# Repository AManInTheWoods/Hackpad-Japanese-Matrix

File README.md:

# CreatePad V1
CreatePad (formerly named "Hackpad V2.1 Japanese Matrix" and "Macropad Proto V1") is a multipurpose productivity macro pad with a 3x3 switch layout, two rotary encoders, an OLED screen and uses QMK firmware. Under the hood is a Japanese Duplex Matrix that made the large amount of inputs (15 in total, including both of the encoders' buttons!) possible. More info on that below.

<H2>
Features: 
</H2>

  * 11 total switches (3x3 MX + 2 knobs)
  
  * A 0.91 inch OLED display
    
  * 10 customizable profiles with VIA support
  
  * Slanted case design for better (my personal) comfort :)

<H2>
CAD Model, Made in Fusion360 (the free version):
</H2>

<H3>This is the overall CAD design of CreatePad:</H3> 

<H3>This is the separated (top case, PCB, bottom case) bodies:</H3> 

<H2>Schematic & PCB (Made in KiCAD):</H2>

<H3>Schematic:</H3>

<H4>"Behold, The Japanese Duplex Matrix"</H4>

<H3>PCB:</H3>

*<H4> I had such a dilemma making sure everything is aligned and symmetrical (some still probably aren't) </H4>*

<H2>Firmware Overview:</H2>

CreatePad uses custom QMK firmware (because the matrix used is different from a traditional matrix) and is highly customizable, even the OLED can be configured using it! The attatched firmware (as of now) can store up to 10 unique, fully customizable configurations (even the knobs' functions!) through VIA.

<H2>The Japanese Duplex Matrix</H2>

Since the XIAO RP2040 only has 14 pins and only 5 of them are left for button inputs, I had to pick between two choices: 1. Reduce the amount of total physical inputs or 2. Find out if there's another type of matrix that reduces the amount of pins even further than that of a traditional matrix. Turns out there is such a thing! It's called a Japanese Duplex Matrix. Everything about it can be read on this webpage: https://kbd.news/The-Japanese-duplex-matrix-1391.html#jpduplex .

In a nutshell, according to the webpage, unlike a traditional keyboard matrix, the custom QMK firmware scans the matrix in both directions! First COL2ROW, then ROW2COL, in succession. "The trick lies in the direction of diodes: two columns are connected to the same COL pin, but one column has diodes pointing in one direction, while switches in the second column have diodes pointing to the opposite direction. This way the matrix can be scanned in both ways, checking half of the switches on the COL2ROW and another half on the ROW2COL iteration." Compared to a traditional matrix, the amount of pins needed have been significant reduced, making it exactly needing only 5 pins! No extra rows or columns needed.

<H2>BOM:</H2>

* 1x Seeed XIAO RP2040 MCU

* 9x MX-Style Switches

* 2x EC11 Rotary Encoders

* 2x Rotary Encoder Knobs

* 11x Through-hole 1N4148 Diodes

* 1x 0.91 Inch OLED Display

* 9x white DSA keycaps

* 4x M3x16mm screws

that's about it for now :). I've learned so much during the process of designing this project, I can't wait to assemble it in the future!

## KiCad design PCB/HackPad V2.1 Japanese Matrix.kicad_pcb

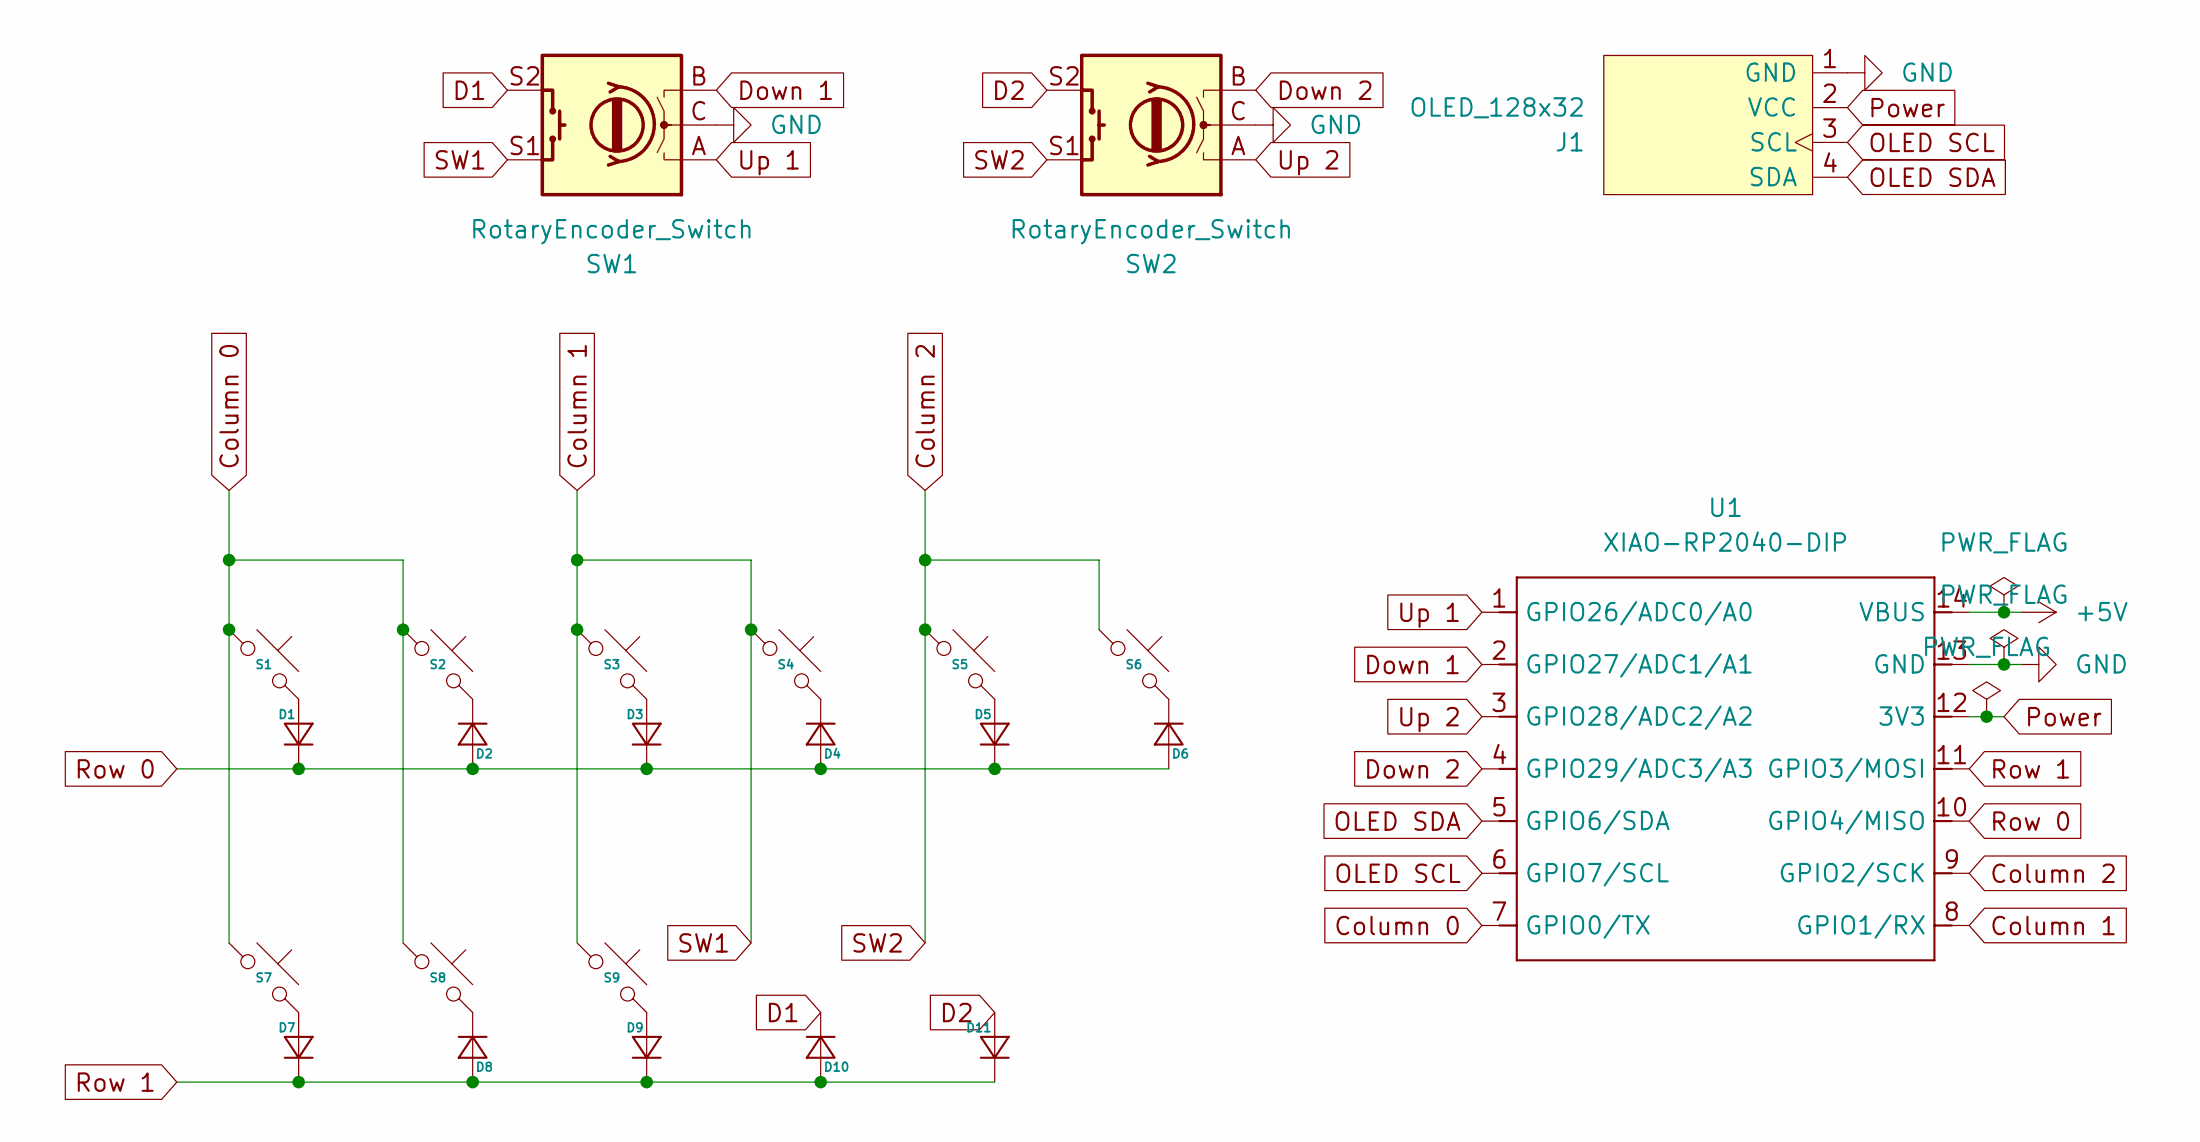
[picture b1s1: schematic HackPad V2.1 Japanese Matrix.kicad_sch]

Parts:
D1, D2, D3, D4, D5, D6, D7, D8, D9, D10, D11: Diode_DO-35
J1: OLED_128x32
S1, S2, S3, S4, S5, S6, S7, S8, S9: MX_PCB_1.00u
SW1, SW2: RotaryEncoder_Switch; RotaryEncoder_Alps_EC11E-Switch_Vertical_H20mm
U1: XIAO-RP2040-DIP

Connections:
+5V: U1.14 (VBUS)
Column 0: S1.1, S2.1, S7.1, S8.1, U1.7 (GPIO0/TX)
Column 1: S3.1, S4.1, S9.1, SW1.S1, U1.8 (GPIO1/RX)
Column 2: S5.1, S6.1, SW2.S1, U1.9 (GPIO2/SCK)
D1: D10.1 (K), SW1.S2
D2: D11.2 (A), SW2.S2
Down 1: SW1.B, U1.2 (GPIO27/ADC1/A1)
Down 2: SW2.B, U1.4 (GPIO29/ADC3/A3)
GND: J1.1 (GND), SW1.C, SW2.C, U1.13 (GND)
unnamed: D1.2 (A), S1.2
unnamed: D2.1 (K), S2.2
unnamed: D3.2 (A), S3.2
unnamed: D4.1 (K), S4.2
unnamed: D5.2 (A), S5.2
unnamed: D6.1 (K), S6.2
unnamed: D7.2 (A), S7.2
unnamed: D8.1 (K), S8.2
unnamed: D9.2 (A), S9.2
OLED SCL: J1.3 (SCL), U1.6 (GPIO7/SCL)
OLED SDA: J1.4 (SDA), U1.5 (GPIO6/SDA)
Power: J1.2 (VCC), U1.12 (3V3)
Row 0: D1.1 (K), D2.2 (A), D3.1 (K), D4.2 (A), D5.1 (K), D6.2 (A), U1.10 (GPIO4/MISO)
Row 1: D7.1 (K), D8.2 (A), D9.1 (K), D10.2 (A), D11.1 (K), U1.11 (GPIO3/MOSI)
Up 1: SW1.A, U1.1 (GPIO26/ADC0/A0)
Up 2: SW2.A, U1.3 (GPIO28/ADC2/A2)

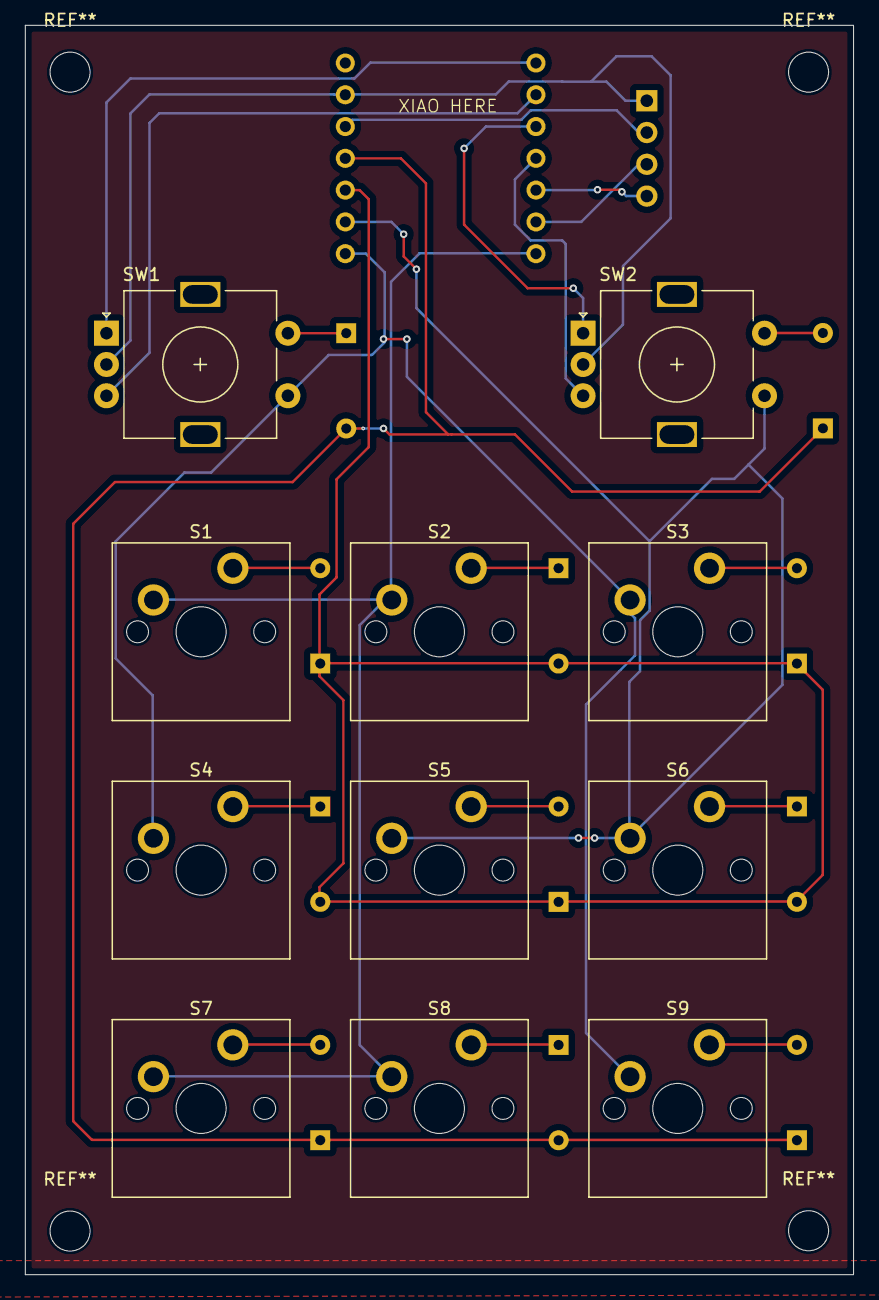
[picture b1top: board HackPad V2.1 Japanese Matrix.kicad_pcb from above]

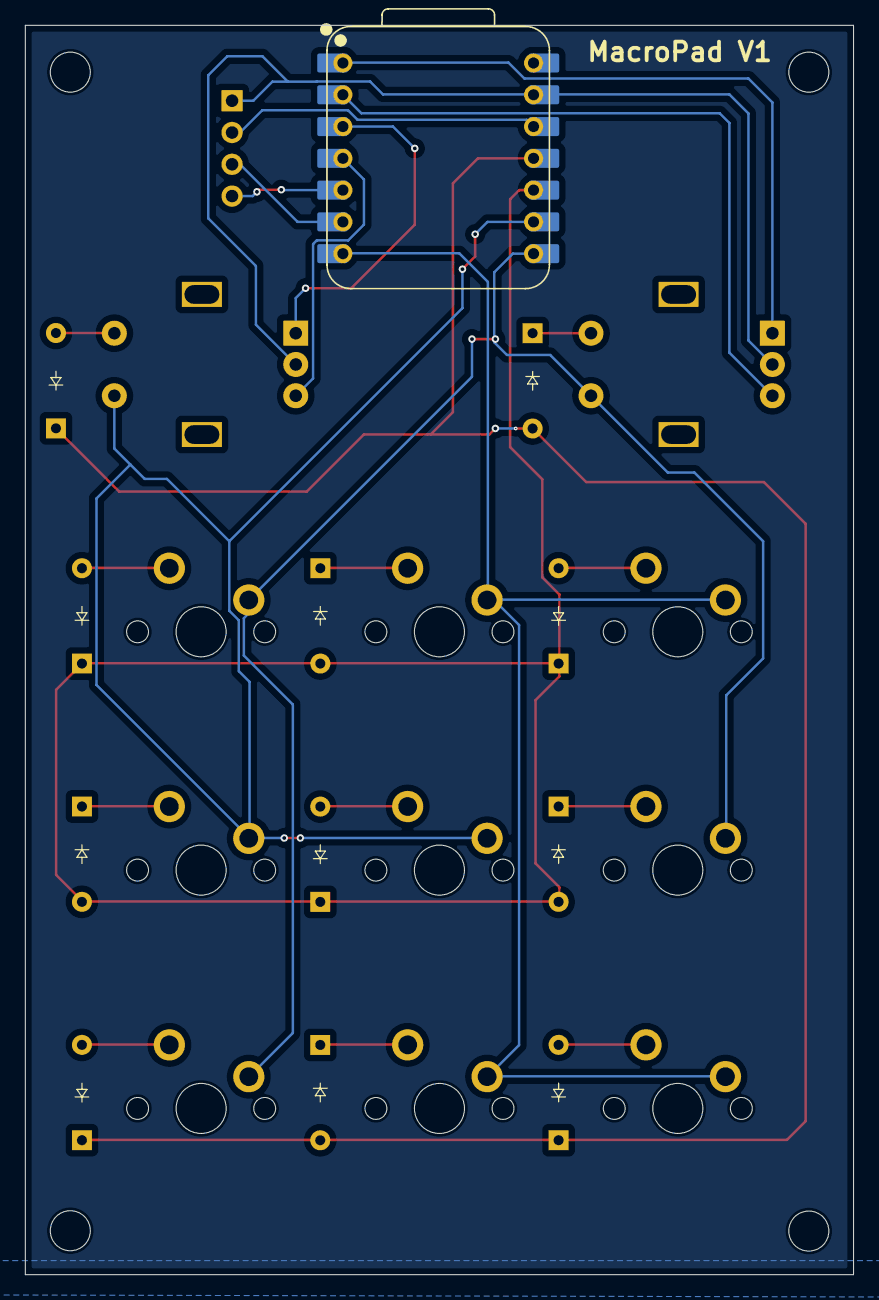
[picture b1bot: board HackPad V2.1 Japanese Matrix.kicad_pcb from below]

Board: 2 copper layers, 66.2 x 99.9 mm, 24 parts (12 on the bottom side), 24 nets.

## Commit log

2026-03-03 Create CAD
2026-03-03 Create ...
2026-03-04 Create fdsfs
2026-03-04 Rename README to README.md
2026-03-06 Fix formatting and enhance README content
    Corrected formatting and improved clarity in the README.
2026-03-06 Change link reference to 'webpage' in README
    Updated the link description for the Japanese Duplex Matrix.
2026-03-06 Add rotary encoder knobs to the parts list
